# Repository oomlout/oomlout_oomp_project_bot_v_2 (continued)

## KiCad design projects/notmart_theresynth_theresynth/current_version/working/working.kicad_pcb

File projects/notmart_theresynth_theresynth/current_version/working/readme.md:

# theresynth
 
## summary 
* id: notmart_theresynth_theresynth
* user: notmart
* name: theresynth
* board: theresynth
* repo: https://github.com/notmart/theresynth
* src_file_repo_kicad_pcb: theresynth.kicad_pcb
* src_file_repo_kicad_pcb_link: https://github.com/notmart/theresynth/tree/master/theresynth.kicad_pcb

* src_file_repo_sch: 
* src_file_repo_sch_link: https://github.com/notmart/theresynth/tree/master/
* full details link: https://github.com/oomlout/oomlout_oomp_project_bot_v_2/tree/main/projects/notmart_theresynth_theresynth/current_version/working

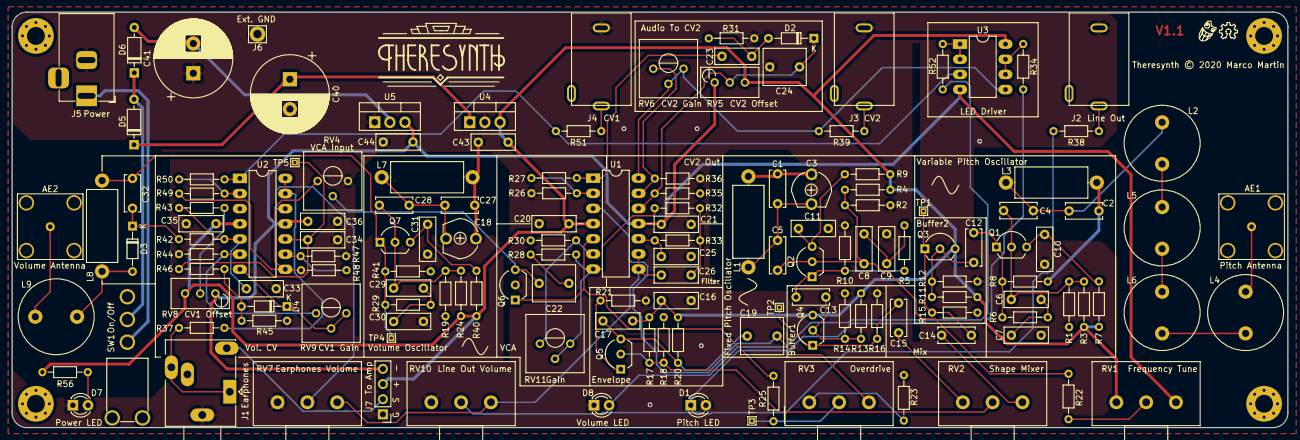
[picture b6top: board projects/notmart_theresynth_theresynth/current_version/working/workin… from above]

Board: 2 copper layers, 214.0 x 69.7 mm, 148 parts (0 on the bottom side), 79 nets.

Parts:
AE1, AE2: Antenna; Connector_F
C1, C2, C14, C15: 22p; C_Disc_D6.0mm_W2.5mm_P5.00mm
C3: 20p; Variable_Capacitor_W6.5mm_P5.00mm
C4: 220p; C_Disc_D6.0mm_W2.5mm_P5.00mm
C5, C28: 330p; C_Disc_D6.0mm_W2.5mm_P5.00mm
C6, C7, C8, C9, C29, C30: 1n; C_Rect_L7.2mm_W2.5mm_P5.00mm_FKS2_FKP2_MKS2_MKP2
C10, C11, C16, C20, C21, C31, C33, C34, C35, C36, C43, C44: 100n; C_Rect_L7.2mm_W2.5mm_P5.00mm_FKS2_FKP2_MKS2_MKP2
C12, C13: 68p; C_Disc_D6.0mm_W2.5mm_P5.00mm
C17: 4.7n; C_Rect_L7.2mm_W2.5mm_P5.00mm_FKS2_FKP2_MKS2_MKP2
C18: 60p; Variable_Capacitor_W6.5mm_P5.00mm
C19, C22, C24: 1u; C_Rect_L7.0mm_W6.0mm_P5.00mm
C23: 2.2n; C_Rect_L7.2mm_W2.5mm_P5.00mm_FKS2_FKP2_MKS2_MKP2
C25, C26: 10n; C_Rect_L7.2mm_W2.5mm_P5.00mm_FKS2_FKP2_MKS2_MKP2
C27: 47p; C_Disc_D6.0mm_W2.5mm_P5.00mm
C32: 100p; C_Disc_D6.0mm_W2.5mm_P5.00mm
C40, C41: 3300u; CP_Radial_D13.0mm_P5.00mm
D1, D7, D8: LED; LED_D3.0mm
D2, D3, D4: 1N4148; D_DO-34_SOD68_P7.62mm_Horizontal
D5, D6: 1N4001; D_DO-35_SOD27_P7.62mm_Horizontal
J1: AudioJack3_Switch; Jack_3.5mm_Ledino_KB3SPRS_Horizontal
J2, J3, J4: AudioJack2; PJ302M
J5: Jack-12V AC; BarrelJack_Horizontal
J6: Ext. GND; Pin_D1.4mm_L8.5mm_W2.8mm_FlatFork
J7: To_Amp; PinHeader_1x04_P2.54mm_Vertical
L1, L3: 4.7mH; L_Axial_L12.0mm_D5.0mm_P15.24mm_Horizontal_Fastron_MISC
L2, L4, L5, L6: 10mH; L_Radial_D12.5mm_P7.00mm_Fastron_09HCP
L7: 4.8m; L_Axial_L12.0mm_D5.0mm_P15.24mm_Horizontal_Fastron_MISC
L8: 1m; L_Axial_L12.0mm_D5.0mm_P15.24mm_Horizontal_Fastron_MISC
L9: 10m; L_Radial_D12.5mm_P7.00mm_Fastron_09HCP
Q1, Q2, Q3, Q4, Q5, Q7: 2N3904; TO-92_Inline_Wide
Q6: J113; TO-92_Inline_Wide
R1, R2, R19: 68k; R_Axial_DIN0204_L3.6mm_D1.6mm_P7.62mm_Horizontal
R3, R4, R24, R27, R45: 100k; R_Axial_DIN0204_L3.6mm_D1.6mm_P7.62mm_Horizontal
R5, R6, R8, R10, R21, R26, R29, R32, R33, R34, R36, R37, R38, R39, R41, R44, R51, R52, R56: 1k; R_Axial_DIN0204_L3.6mm_D1.6mm_P7.62mm_Horizontal
R7, R9, R40: 100; R_Axial_DIN0204_L3.6mm_D1.6mm_P7.62mm_Horizontal
R11, R13, R23: 22k; R_Axial_DIN0204_L3.6mm_D1.6mm_P7.62mm_Horizontal
R12, R14, R18: 47k; R_Axial_DIN0204_L3.6mm_D1.6mm_P7.62mm_Horizontal
R15, R16, R20, R30, R31, R47, R48, R49, R50: 10k; R_Axial_DIN0204_L3.6mm_D1.6mm_P7.62mm_Horizontal
R17: 470k; R_Axial_DIN0204_L3.6mm_D1.6mm_P7.62mm_Horizontal
R22, R43: 330k; R_Axial_DIN0204_L3.6mm_D1.6mm_P7.62mm_Horizontal
R25, R28, R42, R46: 220k; R_Axial_DIN0204_L3.6mm_D1.6mm_P7.62mm_Horizontal
R35: 1M; R_Axial_DIN0204_L3.6mm_D1.6mm_P7.62mm_Horizontal
RV1, RV2, RV3: 100k; Potentiometer_Alps_RK163_Single_Horizontal
RV4: 10k; Potentiometer_Bourns_3386P_Vertical
RV5, RV8: 100k; Potentiometer_Bourns_3296W_Vertical
RV6, RV9, RV11: 100k; Potentiometer_Bourns_3386P_Vertical
RV7, RV10: 10k; Potentiometer_Alps_RK163_Single_Horizontal
SW1: SW_SPST; Horizontal_SPDT
TP1, TP2, TP3, TP4, TP5: TestPoint; TestPoint_THTPad_1.0x1.0mm_Drill0.5mm
U1, U2: TL074; DIP-14_W7.62mm_LongPads
U3: TL072; DIP-8_W7.62mm_LongPads
U4: LM7812_TO220; TO-220-3_Vertical
U5: LM7912_TO220; TO-220-3_Vertical

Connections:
+12V: C16.1, C17.1, C20.1, C35.1, C43.1, J7.3, Q3.3, Q4.3, R3.2, R4.2, R7.1, R9.1, R11.1, R13.1, R17.1, R20.1, R24.1, R40.1, R56.2, RV1.1, RV5.3, RV8.3, U1.4, U2.4, U3.8, U4.3
-12V: C21.1, C36.1, C44.2, J7.4, RV1.3, RV5.1, RV8.1, U1.11, U2.11, U3.4, U5.3
/Audio Processing/RawAudioIn: C17.2, C19.2, Q5.3, R20.2
/Audio Processing/VolumeControlIn: R48.2, R49.2, RV4.1, U2.8
GND: C1.2, C2.2, C3.2, C7.2, C9.2, C10.1, C11.1, C16.2, C18.2, C20.2, C21.2, C24.2, C25.2, C27.2, C30.2, C31.1, C33.2, C34.2, C35.2, C36.2, C40.2, C41.1, C43.2, C44.1, D1.2, D7.1, D8.1, J1.S, J2.S, J3.S, J4.S, J5.2, J6.1, J7.1, L1.2, L3.2, L7.2, Q6.2, R1.2, R2.2, R8.2, R10.2, R12.2, R14.2, R15.2, R16.2, R18.2, R19.2, R21.2, R23.2, R26.1, R30.2, R31.1, R35.2, R36.1, R41.2, R44.1, R45.2, R47.2, RV4.3, RV7.1, RV10.1, U2.3, U4.2, U5.1
unnamed: AE1.1, L4.1
unnamed: AE2.1, L9.1
unnamed: C1.1, C3.1, C5.2, L1.1
unnamed: C2.1, C4.1, L2.2, L3.1
unnamed: C4.2, C6.1, Q1.2, R1.1, R3.1
unnamed: C5.1, C8.1, Q2.2, R2.1, R4.1, R22.1
unnamed: C6.2, C7.1, R6.2
unnamed: C8.2, C9.1, R5.2
unnamed: C10.2, Q1.3, R7.2
unnamed: C11.2, Q2.3, R9.2
unnamed: C12.1, Q3.2, R11.2, R12.1
unnamed: C12.2, Q1.1, R6.1, R8.1
unnamed: C13.1, Q4.2, R13.2, R14.1
unnamed: C13.2, Q2.1, R5.1, R10.1
unnamed: C14.1, Q3.1, R15.1, TP1.1
unnamed: C14.2, RV2.3
unnamed: C15.1, RV2.1
unnamed: C15.2, Q4.1, R16.1, TP2.1
unnamed: C18.1, C27.1, C28.2, L7.1
unnamed: C19.1, RV3.3, U1.3
unnamed: C22.1, R28.2
unnamed: C22.2, Q6.3, RV4.2
unnamed: C23.1, D2.2, R31.2
unnamed: C23.2, R27.1, U1.1
unnamed: C24.1, D2.1, R35.1, RV5.2, U1.12
unnamed: C25.1, R33.1, U1.10
unnamed: C26.1, RV7.3, RV10.3, U1.8, U1.9
unnamed: C26.2, R32.1, R33.2
unnamed: C28.1, C29.1, Q7.2, R19.1, R24.2
unnamed: C29.2, C30.1, R29.2
unnamed: C31.2, Q7.3, R40.2
unnamed: C32.1, L8.2, Q7.1, R29.1, R41.1, TP4.1
unnamed: C32.2, D3.1, R42.2
unnamed: C33.1, R42.1, R43.1, U2.5
unnamed: C34.1, R46.1, TP5.1, U2.10
unnamed: C40.1, D5.1, U4.1
unnamed: C41.2, D6.2, U5.2
unnamed: D1.1, R34.1
unnamed: D3.2, L8.1, L9.2
unnamed: D4.1, RV9.2, RV9.3, U2.7
unnamed: D4.2, R45.1, R46.2
unnamed: D5.2, D6.1, SW1.2
unnamed: D7.2, R56.1
unnamed: D8.2, R52.1
unnamed: J1.R, J1.T, R37.1
unnamed: J1.TN, J7.2
unnamed: J2.T, R38.1
unnamed: J3.T, R39.1
unnamed: J4.T, R51.1
unnamed: J5.1, SW1.1
unnamed: L2.1, L5.2
unnamed: L4.2, L6.1
unnamed: L5.1, L6.2
unnamed: Q5.1, R21.1
unnamed: Q5.2, R17.2, R18.1, RV2.2
unnamed: Q6.1, R25.1, U1.5
unnamed: R22.2, RV1.2
unnamed: R23.1, RV3.1
unnamed: R25.2, RV3.2, TP3.1
unnamed: R26.2, R27.2, U1.2
unnamed: R28.1, R32.2, RV11.2, RV11.3, U1.7
unnamed: R30.1, RV11.1, U1.6
unnamed: R34.2, U3.6, U3.7
unnamed: R36.2, RV6.1, U1.13
unnamed: R37.2, U2.13, U2.14
unnamed: R38.2, RV10.2
unnamed: R39.2, RV6.2, RV6.3, U1.14, U3.5
unnamed: R43.2, RV8.2
unnamed: R44.2, RV9.1, U2.6
unnamed: R47.1, R48.1, U2.9
unnamed: R49.1, R50.1, U2.2
unnamed: R50.2, R51.2, U2.1, U3.3
unnamed: R52.2, U3.1, U3.2
unnamed: RV7.2, U2.12
